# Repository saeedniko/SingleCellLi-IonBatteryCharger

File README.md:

# SingleCellLi-IonBatteryCharger

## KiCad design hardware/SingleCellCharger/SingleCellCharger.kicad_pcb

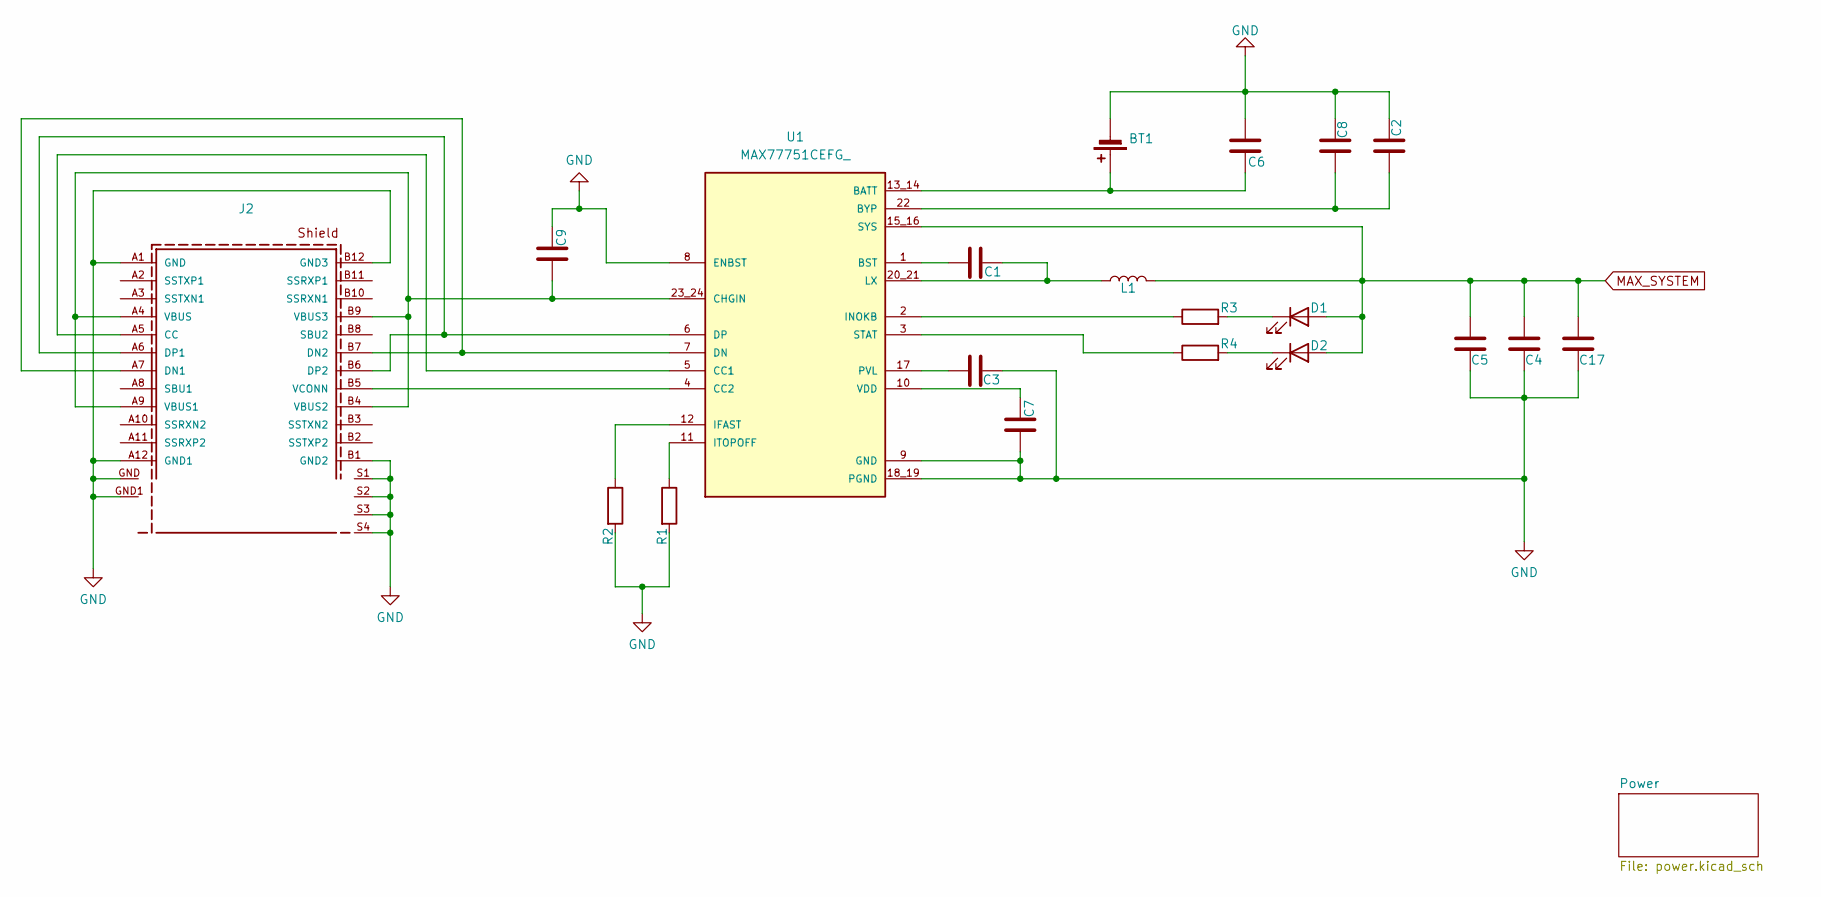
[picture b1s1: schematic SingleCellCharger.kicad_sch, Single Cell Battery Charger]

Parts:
BT1: Battery_Cell; BatteryHolder_Keystone_2466_1xAAA
C1: 100nF/6V3; C_0603_1608Metric_Pad1.08x0.95mm_HandSolder
C2: 22µF/16V; C_0603_1608Metric_Pad1.08x0.95mm_HandSolder
C3, C7, C9: 2.2µF/10V; C_0603_1608Metric_Pad1.08x0.95mm_HandSolder
C4, C5: 10µF; C_0603_1608Metric_Pad1.08x0.95mm_HandSolder
C6: 10µF/10V; C_0603_1608Metric_Pad1.08x0.95mm_HandSolder
C8: 10µF/16V; C_0603_1608Metric_Pad1.08x0.95mm_HandSolder
C17: 4700PF; C_0603_1608Metric_Pad1.08x0.95mm_HandSolder
D1: LED; LED_0603_1608Metric_Pad1.05x0.95mm_HandSolder
D2: LED red; LED_0603_1608Metric_Pad1.05x0.95mm_HandSolder
J2: USB3.1 TYPEC 24P SMD RA; 632723100011; PART-NUMBER 632723100011
L1: 47µH; L_Coilcraft_LPS5030
R1: 8K06; R_0603_1608Metric_Pad0.98x0.95mm_HandSolder
R2: 2K4; R_0603_1608Metric_Pad0.98x0.95mm_HandSolder
R3, R4: 470R; R_0603_1608Metric_Pad0.98x0.95mm_HandSolder
U1: MAX77751CEFG_; IC_MAX77751FEFG_; PARTREV 3

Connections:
GND: BT1.2 (-), C2.2, C3.2, C4.2, C5.2, C6.1, C7.1, C8.2, C9.2, C17.2, J2.A1 (GND), J2.A12 (GND1), J2.B1 (GND2), J2.B12 (GND3), J2.GND, J2.GND1, J2.S1, J2.S2, J2.S3, J2.S4, R1.2, R2.2, U1.8 (ENBST), U1.9 (GND), U1.18_19 (PGND); also elsewhere on the board
MAX_SYSTEM: C4.1, C5.1, C17.1, D1.2 (A), D2.2 (A), L1.2, U1.15_16 (SYS); also elsewhere on the board
unnamed: BT1.1 (+), C6.2, U1.13_14 (BATT)
unnamed: D1.1 (K), R3.2
unnamed: D2.1 (K), R4.2
unnamed: J2.A5 (CC), U1.5 (CC1)
unnamed: J2.A7 (DN1), J2.B7 (DN2), U1.7 (DN)
unnamed: J2.A6 (DP1), J2.B6 (DP2), U1.6 (DP)
unnamed: C9.1, J2.A4 (VBUS), J2.A9 (VBUS1), J2.B4 (VBUS2), J2.B9 (VBUS3), U1.23_24 (CHGIN)
unnamed: J2.B5 (VCONN), U1.4 (CC2)
unnamed: C1.1, U1.1 (BST)
unnamed: C2.1, C8.1, U1.22 (BYP)
unnamed: R2.1, U1.12 (IFAST)
unnamed: R3.1, U1.2 (INOKB)
unnamed: R1.1, U1.11 (ITOPOFF)
unnamed: C1.2, L1.1, U1.20_21 (LX)
unnamed: C3.1, U1.17 (PVL)
unnamed: R4.1, U1.3 (STAT)
unnamed: C7.2, U1.10 (VDD)

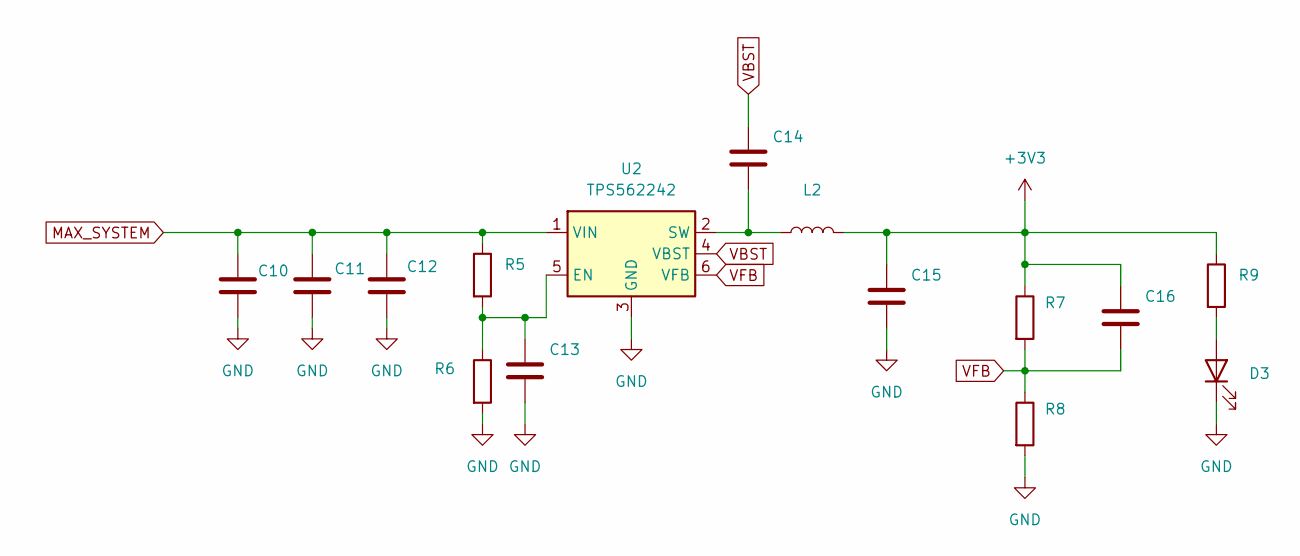
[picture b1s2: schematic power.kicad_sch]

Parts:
C10, C11: 10u/25V; C_1206_3216Metric
C12, C14: 100n/50V; C_0603_1608Metric
C13: 10n/50V; C_1206_3216Metric
C15: 22u/10V; C_1206_3216Metric; MPN 81-GRM31CR71A226K15L
C16: 33p/50V; C_0603_1608Metric
D3: LED_green; LED_0603_1608Metric_Pad1.05x0.95mm_HandSolder; MPN 710-150060VS75000
L2: 2u2; L_Taiyo-Yuden_NR-24xx; MPN 963-NRH2410T2R2MN
R5: 47k; R_0603_1608Metric
R6: 20k; R_0603_1608Metric
R7: 75K; R_0603_1608Metric
R8: 24k; R_0603_1608Metric
R9: 270R; R_0603_1608Metric
U2: TPS562242; SOT-563; MPN 595-TPS562242DRLR

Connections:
+3V3: C15.1, C16.1, L2.2, R7.1, R9.1
GND: C10.2, C11.2, C12.2, C13.2, C15.2, D3.1 (K), R6.2, R8.2, U2.3 (GND); also elsewhere on the board
MAX_SYSTEM: C10.1, C11.1, C12.1, R5.1, U2.1 (VIN); also elsewhere on the board
unnamed: D3.2 (A), R9.2
unnamed: C13.1, R5.2, R6.1, U2.5 (EN)
unnamed: C14.2, L2.1, U2.2 (SW)
VBST: C14.1, U2.4 (VBST)
VFB: C16.2, R7.2, R8.1, U2.6 (VFB)

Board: 2 copper layers, 35 parts (20 on the bottom side), 25 nets, no tracks yet.

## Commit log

2024-12-21 Start with schematic
2024-12-21 Insert USB_C connector
2024-12-22 Add fottprints
2024-12-22 Add USB-C connector
2024-12-26 Add new sheet
2024-12-29 Add dc/dc
2025-03-15 start with PCB
2025-03-15 update 3D
2025-03-23 update pcb
